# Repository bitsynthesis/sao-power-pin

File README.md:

# SAO Power Pin

A PCB to provide switchable, stand-alone battery power to a [shitty add-on](https://hackaday.com/2019/03/20/introducing-the-shitty-add-on-v1-69bis-standard/).

Project created with [Kicad 5](http://www.kicad-pcb.org).

# License

Copyright Ben Baker-Smith 2019.

This documentation describes Open Hardware and is licensed under the
[CERN OHL v.1.2](/LICENSE.TXT).

You may redistribute and modify this documentation under the terms of the
CERN OHL v.1.2. This documentation is distributed
WITHOUT ANY EXPRESS OR IMPLIED WARRANTY, INCLUDING OF
MERCHANTABILITY, SATISFACTORY QUALITY AND FITNESS FOR A
PARTICULAR PURPOSE. Please see the CERN OHL v.1.2 for applicable
conditions

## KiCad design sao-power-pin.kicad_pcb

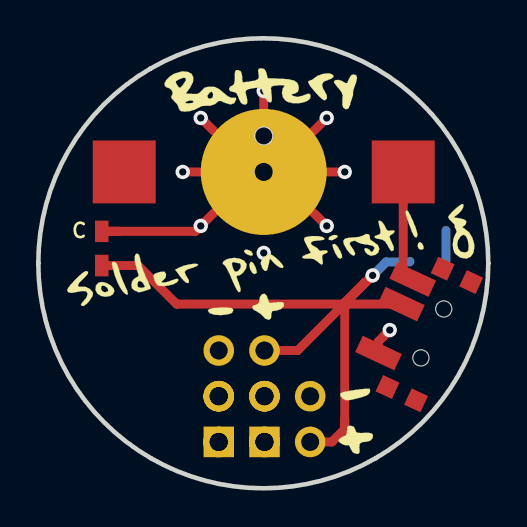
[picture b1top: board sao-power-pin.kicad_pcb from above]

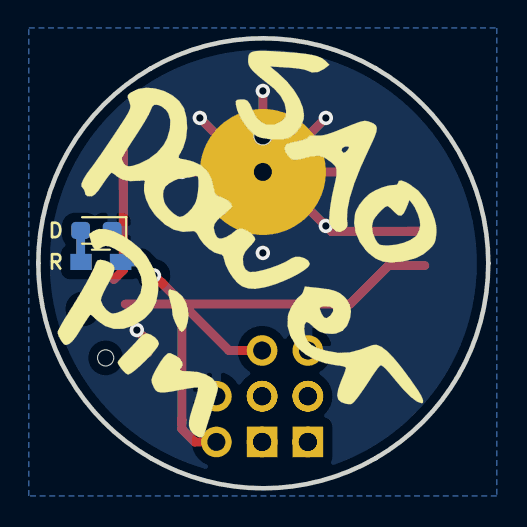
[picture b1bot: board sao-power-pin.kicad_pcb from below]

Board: 2 copper layers, 25.0 x 25.0 mm, 8 parts (2 on the bottom side), 4 nets.

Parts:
BATTERY1: Battery_Cell; BatteryHolder12_5mm_cell_Harwin_S8201-46R_NoSilk
C: C; C_0603_HandSoldering
D: LED; LED_0603_1608Metric_Pad1.05x0.95mm_HandSolder
JH1: Conn_02x03_Odd_Even; Pin_Header_Straight_2x03_Pitch2.54mm
JV1: Conn_02x03_Odd_Even; Pin_Header_Straight_2x03_Pitch2.54mm
POW1: SW_SPST; SPDT_LowProfile_SMD_Switch_PCM12SMTR_NoSilk
PUSH PIN: PushPin
R: R_Small; R_0603_HandSoldering

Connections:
+3V0: BATTERY1.1, POW1.3
/+V: C.1, JH1.5, JV1.5, POW1.2, R.1
GND: BATTERY1.2, C.2, D.1, JH1.6, JV1.6, POW1.1, PUSH PIN.1
unnamed: D.2, R.2

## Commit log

2019-10-15 Init
2019-10-21 Prepare v1.0.0 release
